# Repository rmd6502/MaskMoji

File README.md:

# MaskMoji

A way to let people see your facial expressions through a mask

# Instructions

I based my build on the [LilyGo TTGO](https://www.tindie.com/products/ttgo/lilygor-ttgo-t-display/) since it had everything I needed on the board already.

Git clone or download and unpack this repository to a convenient location.

## Prepare the board

You'll need to purchase a small square or rectangular rechargable lithium ion battery, [for example](https://www.sparkfun.com/products/13851). While you're there, maybe buy four [magnets](https://www.sparkfun.com/products/8914) to help hold the assembly to your mask.

The battery comes with a 1mm or 2mm connector, but the TTGO comes with a 1.25mm connector. You'll need to clip off the leads and solder on the 1.25mm connector. Be careful not to short the battery while doing this.

I 3D printed an [enclosure](https://www.thingiverse.com/thing:4183337) which holds the board and battery and protects the screen from cracking.

Download and install the [Arduino IDE](https://arduino.cc), the [ESP32 board support](https://github.com/espressif/arduino-esp32/blob/master/docs/arduino-ide/boards_manager.md), and the [SPIFFS Filesystem loader](https://github.com/me-no-dev/arduino-esp32fs-plugin).

Open the Arduino IDE, and install the plugins above if you haven't already. Go to Tools->Library Manager and search for and install the Adafruit ST7789 library and its dependencies. Install the TJpg decoder.

Go to Tools->board and select ESP32->ESP32 Dev Board. Go to Tools->Partition Scheme and select "No OTA (1MB App/3MB SPIFFS)". Don't select the 3MB FAT option, that won't work.

You'll need to thin out the data directory to make it fit in 3MB. If you have the 16MB version of the TTGO and are feeling brave, you can modify {ARDUINO_ROOT}/packages/esp32/hardware/esp32/1.0.4/boards.txt and find the 7MB SPIFFS option and move it to the description for the ESP32 dev board.

Open the Maskmoji firmware at (unpack directory)/Firmware/MaskMoji/MaskMoji.ino . Click the check mark icon at the top left to build and make sure it succeeds.

Plug in your board. Go to Tools->Port and select the COM or /dev/tty that corresponds to your board.

Click the arrow icon to the right of the checkmark icon, this should upload the firmware to your board. Assuming you installed the ESPFS loader, go to Tools->ESP32 Sketch Data Upload. This uploads the Emoji images to the flash memory.

## iPhone App (No Android App yet)

If you have a mac, you can build and install the app via XCode. If not, I'll eventually have something on the App Store.

## Usage

Open the MaskMoji app on your iPhone.
Plug the battery into your board.

Select "Scan" in the upper right. You should see your maskmoji. If there are multiple, press the button on the same side as the reset button to see your maskmoji's ID. Select your maskmoji. You'll return to the emoji grid.

Click an emoji to display it on the screen!

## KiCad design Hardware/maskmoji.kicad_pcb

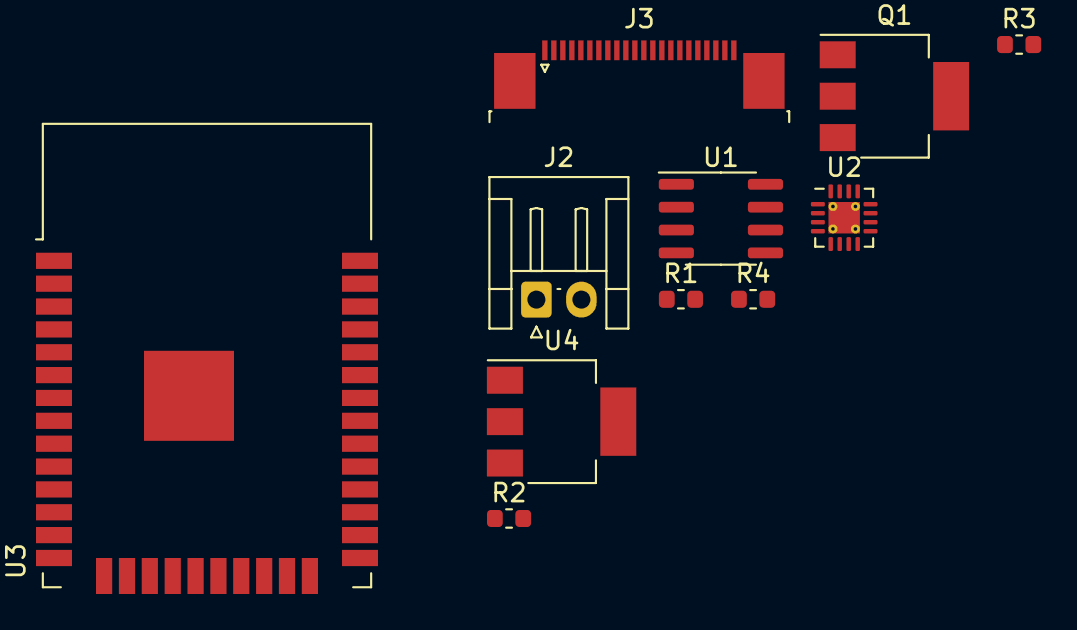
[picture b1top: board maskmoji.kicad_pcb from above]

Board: 2 copper layers, 11 parts (0 on the bottom side), 6 nets, no tracks yet.

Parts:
J2: Conn_01x02; JST_EH_S2B-EH_1x02_P2.50mm_Horizontal
J3: Conn_01x22; TE_2-1734839-2_1x22-1MP_P0.5mm_Horizontal
Q1: PZT2222A; SOT-223-3_TabPin2
R1, R2, R3, R4: R; R_0603_1608Metric
U1: CH330N; SOIC-8_3.9x4.9mm_P1.27mm
U2: BQ24075; QFN-16-1EP_3x3mm_P0.5mm_EP1.75x1.75mm_ThermalVias
U3: ESP32-WROOM-32
U4: LM1117-3.3; SOT-223

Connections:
+3V3: U3.2, U4.2
GND: Q1.3, R4.2, U1.3, U2.8, U3.1, U3.15, U3.38, U3.39, U4.1
unnamed: Q1.1, R3.1, R4.1
unnamed: U1.6, U3.35
unnamed: U1.7, U3.34
unnamed: U2.10, U2.11, U4.3

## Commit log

2020-09-13 Initial structure
2020-09-14 bluetooth scan
2020-09-19 bluetooth stuff
2020-09-19 initial schematic
2020-09-24 add firmware dir
2020-09-30 latest firmware
2020-10-01 advertise bluetooth
2020-10-01 cleanups
2020-10-02 add ident
2020-10-02 bluetooth scan, etc
2020-10-02 ui tweaks
2020-10-02 more ui tweaks
2020-10-02 icon
2020-10-02 prevent dups
2020-10-02 add more error checking, support for more emojis
2020-10-02 add more mojis
2020-10-03 colors, layout
2020-10-03 even more mojis
2020-10-03 attempt to reconnect to last connected device
2020-10-05 Fix setting connected device at wrong place
2020-10-09 add all the emoji for 16MB flash
2020-10-10 allow rearranging the collection view
2020-10-15 Start adding customization for emoji list
2020-10-16 allow editing of moji collection
2020-10-19 select, scale, and convert an image
2020-10-19 add comments including future plans.
2020-10-19 accept image data
2020-10-19 match firmware characteristic ids
2020-10-19 remove unneeded init.
2020-10-19 commentary
2020-10-19 simplify
2020-10-20 write data to service. also, add characteristic to service.
2020-10-20 add debug
2020-10-21 query all characteristics available
2020-10-21 take more control of image conversion
2020-10-21 dismiss when image selected
2020-10-22 hack to make images work
2020-10-23 bump version
2020-10-23 background image processing
2020-10-23 add duration characteristic
2020-10-24 fix memory issue in onRead?
2020-10-24 tabs
2020-10-24 send image receives all characteristics.
2020-10-24 Reconnect on lost connection
2020-10-25 update bundle version
2020-11-01 naive settings view
2020-11-01 support pre-14 for now
2020-11-01 set duration property
2020-11-01 debugging
2020-11-01 fix math
2020-11-02 fix segue bug
2020-11-02 move toggle emoji into settings
2020-11-02 fix settings table?
2020-11-18 make settings button more intuitive
2020-11-28 save settings in nvm
